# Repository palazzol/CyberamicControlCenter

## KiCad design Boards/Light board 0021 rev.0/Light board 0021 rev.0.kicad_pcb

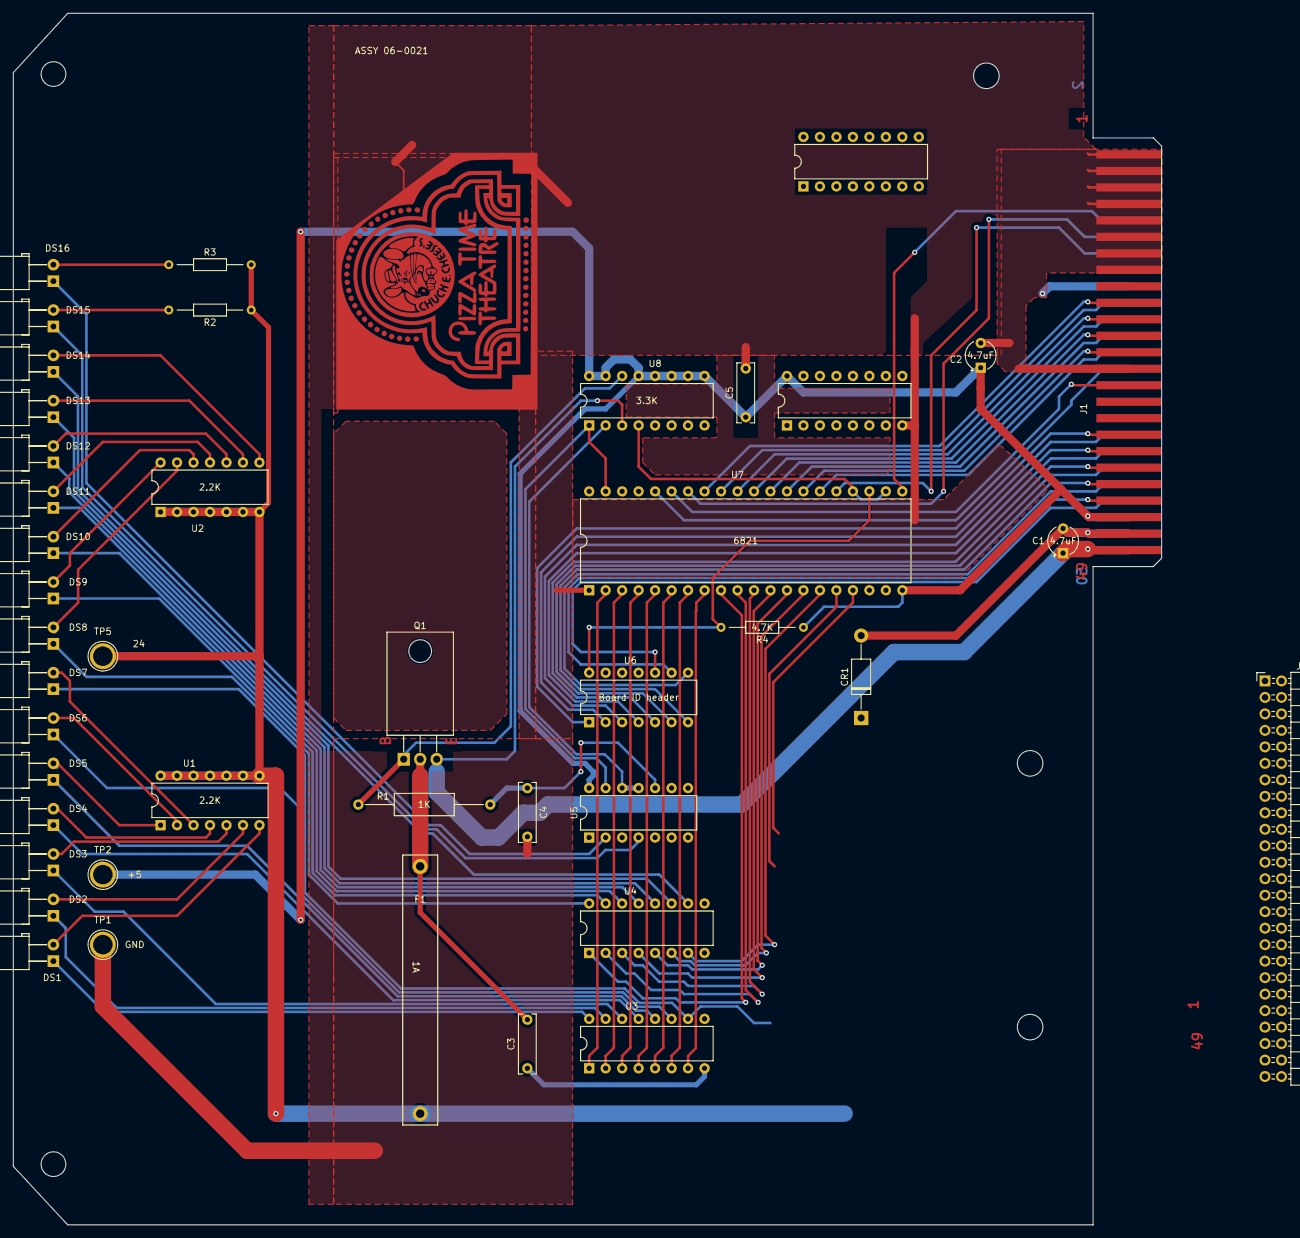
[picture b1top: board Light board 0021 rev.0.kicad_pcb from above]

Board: 2 copper layers, 176.9 x 186.7 mm, 43 parts (0 on the bottom side), 83 nets.

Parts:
C1, C2: 4.7uF; CP_Radial_Tantal_D4mm_P3.81mm
C3, C4, C5: 10nF; C_Rect_L9.0mm_W2.5mm_P7.50mm_MKT
CR1: 1N4001; D_DO-41_SOD81_P12.70mm_Horizontal
DS1, DS2, DS3, DS4, DS5, DS6, DS7, DS8, DS9, DS10, DS11, DS12, DS13, DS14, DS15, DS16: LED; LED_D5.0mm_Horizontal_O3.81mm_Z15.0mm reversed
F1: 1A; Fuseholder_Littelfuse_445_030_series_5x30mm
J1: card edge; Chuck_E_Cheese_small_card_edge
J2: light connector; PinHeader_2x25_P2.54mm_Horizontal
Q1: 2N6125; TO-220-3_Horizontal_TabDown
R1: 1K; R_Axial_DIN0309_L9.0mm_D3.2mm_P20.32mm_Horizontal
R2, R3: 2.2K; R_Axial_DIN0204_L3.6mm_D1.6mm_P12.7mm_Horizontal
R4: 4.7K; R_Axial_DIN0204_L3.6mm_D1.6mm_P12.7mm_Horizontal
TP1: GND; TestPoint_Plated_Hole_D3.0mm
TP2: +5; TestPoint_Plated_Hole_D3.0mm
TP5: 24; TestPoint_Plated_Hole_D3.0mm
U1, U2: 2.2K; DIP-14_W7.62mm
U3, U4: ULN2003A; DIP-16_W7.62mm
U5: 7406; DIP-14_W7.62mm
U6: Board ID header; DIP-14_W7.62mm
U7: 6821; DIP-40_W15.24mm
U8: 3.3K; DIP-16_W7.62mm
U14, U16: Unused DIP; DIP-16_W7.62mm

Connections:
5V: C2.1, C5.1, J1.45, J1.46, R4.1, TP2.1, U5.14 (VCC), U7.20 (VCC), U8.9 (R8.2), U8.10 (R7.2), U8.11 (R6.2), U8.12 (R5.2), U8.13 (R4.2), U8.15 (R2.2), U8.16 (R1.2), U14.16 (R1.2)
5Vpu: U5.11, U5.12, U8.2 (R2.1)
24R: C1.2, C3.1, CR1.2 (A), J1.47, J1.48, J2.2, J2.4, J2.6, J2.8, U3.8 (GND), U4.8 (GND)
24V: C1.1, J1.49, J1.50, Q1.3 (E), U8.3 (R3.1)
24Vout: F1.2, J2.1, J2.49, R2.2, R3.2, TP5.1, U1.8 (R7.2), U1.9 (R6.2), U1.10 (R5.2), U1.11 (R4.2), U1.12 (R3.2), U1.13 (R2.2), U1.14 (R1.2), U2.1 (R1.1), U2.2 (R2.1), U2.3 (R3.1), U2.4 (R4.1), U2.5 (R5.1), U2.6 (R6.1), U2.7 (R7.1), U3.9 (COM), U4.9 (COM)
24Vpu: Q1.1 (B), R1.1, U8.14 (R3.2)
A0out: DS1.1 (K), J2.47, U3.16 (O1)
A1out: DS2.1 (K), J2.45, U3.15 (O2)
A2out: DS3.1 (K), J2.43, U3.14 (O3)
A3out: DS4.1 (K), J2.41, U3.13 (O4)
A4out: DS5.1 (K), J2.39, U3.12 (O5)
A5out: DS6.1 (K), J2.37, U3.11 (O6)
A6out: DS7.1 (K), J2.35, U3.10 (O7)
A7out: DS8.1 (K), J2.33, U4.16 (O1)
B0out: DS9.1 (K), J2.31, U4.15 (O2)
B1out: DS10.1 (K), J2.29, U4.14 (O3)
B2out: DS11.1 (K), J2.27, U4.13 (O4)
B3out: DS12.1 (K), J2.25, U4.12 (O5)
B4out: DS13.1 (K), J2.23, U4.11 (O6)
B5out: DS14.1 (K), J2.21, U4.10 (O7)
B6out: DS15.1 (K), J2.19, U5.4
B7out: DS16.1 (K), J2.17, U5.2
BA0: J1.28, U7.36 (RS0)
BA1: J1.29, U7.35 (RS1)
BS1: J1.35, U6.1
BS2: J1.36, U6.2
BS3: J1.37, U6.3
BS4: J1.38, U6.4
BS5: J1.39, U6.5
BS6: J1.40, U6.6
BS7: J1.41, U6.7
BS8: J1.42, U6.8
BS9: J1.43, U6.9
BS10: J1.44, U6.10
CA2: U5.13, U7.39 (CA2), U8.1 (R1.1)
CS: U7.22 (CS0), U7.24 (CS1), U8.4 (R4.1)
DBB0: J1.19, U7.33 (D0)
DBB1: J1.20, U7.32 (D1)
DBB2: J1.21, U7.31 (D2)
DBB3: J1.22, U7.30 (D3)
DBB4: J1.23, U7.29 (D4)
DBB5: J1.24, U7.28 (D5)
DBB6: J1.25, U7.27 (D6)
DBB7: J1.26, U7.26 (D7)
GND: C2.2, C4.2, C5.2, CR1.1 (K), J1.1, J1.3, J1.5, J1.7, J1.9, J1.11, J1.13, J1.15, J1.18, J1.27, TP1.1, U5.7 (GND), U7.1 (VSS), U14.8 (R8.1)
unnamed: C4.1, R1.2, U5.10
unnamed: DS1.2 (A), U1.7 (R7.1)
unnamed: DS2.2 (A), U1.6 (R6.1)
unnamed: DS3.2 (A), U1.5 (R5.1)
unnamed: DS4.2 (A), U1.4 (R4.1)
unnamed: DS5.2 (A), U1.1 (R1.1)
unnamed: DS6.2 (A), U1.2 (R2.1)
unnamed: DS7.2 (A), U1.3 (R3.1)
unnamed: DS8.2 (A), U2.13 (R2.2)
unnamed: DS9.2 (A), U2.14 (R1.2)
unnamed: DS10.2 (A), U2.12 (R3.2)
unnamed: DS11.2 (A), U2.11 (R4.2)
unnamed: DS12.2 (A), U2.10 (R5.2)
unnamed: DS13.2 (A), U2.9 (R6.2)
unnamed: DS14.2 (A), U2.8 (R7.2)
unnamed: DS15.2 (A), R2.1
unnamed: DS16.2 (A), R3.1
unnamed: C3.2, F1.1, Q1.2 (C)
unnamed: R4.2, U6.14, U7.23 (~CS2)
PA0: U3.1 (I1), U7.2 (PA0)
PA1: U3.2 (I2), U7.3 (PA1)
PA2: U3.3 (I3), U7.4 (PA2)
PA3: U3.4 (I4), U7.5 (PA3)
PA4: U3.5 (I5), U7.6 (PA4)
PA5: U3.6 (I6), U7.7 (PA5)
PA6: U3.7 (I7), U7.8 (PA6)
PA7: U4.1 (I1), U7.9 (PA7)
PB0: U4.2 (I2), U7.10 (PB0)
PB1: U4.3 (I3), U7.11 (PB1)
PB2: U4.4 (I4), U7.12 (PB2)
PB3: U4.5 (I5), U7.13 (PB3)
PB4: U4.6 (I6), U7.14 (PB4)
PB5: U4.7 (I7), U7.15 (PB5)
PB6: U5.3, U7.16 (PB6)
PB7: U5.1, U7.17 (PB7)
PHI2: J1.14, U7.25 (ENABLE)
R/~W: J1.10, U7.21 (R/~W)
~MRST: J1.12, U7.34 (~RESET)

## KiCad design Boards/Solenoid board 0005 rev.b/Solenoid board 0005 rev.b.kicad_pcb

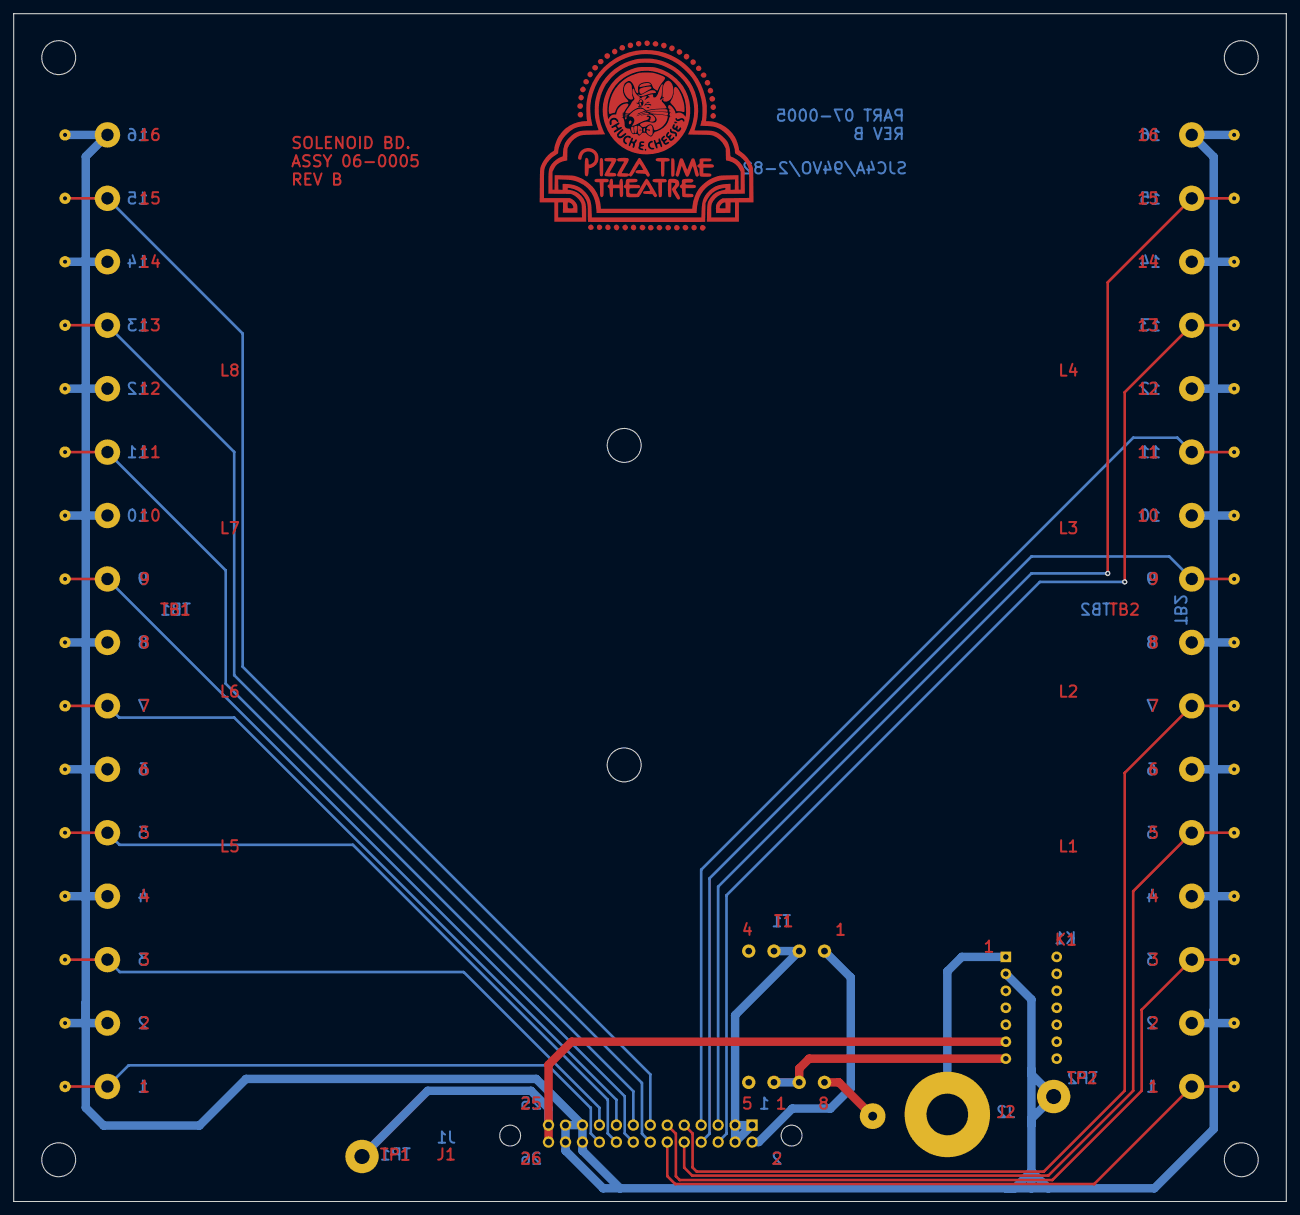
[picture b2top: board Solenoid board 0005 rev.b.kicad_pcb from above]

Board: 2 copper layers, 190.6 x 177.9 mm, 8 parts (0 on the bottom side), 23 nets.

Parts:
J1: character connector; PinHeader_2x13_P2.54mm_Horizontal
J2: Conn_Coaxial; Jack_6.35mm_Neutrik_NJ2FD-V_Vertical
K1: DIP relay; DIP-14_W7.62mm
T1: Transformer_SP_2S; Transformer_Coilcraft_Q4434-B_Rhombus-T1311
TB1, TB2: Conn_01x16_Pin; TerminalBlock_Dinkle_DT-55-B01X-16_P10.00mm
TP1: GND; TestPoint_Plated_Hole_D3.0mm
TP2: 24v; TestPoint_Plated_Hole_D3.0mm

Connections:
24R: J1.25, J1.26, K1.6, TP1.1
+24VDC: J1.21, J1.22, J1.23, J1.24, K1.2, TB1.2, TB1.4, TB1.6, TB1.8, TB1.10, TB1.12, TB1.14, TB1.16, TB2.2, TB2.4, TB2.6, TB2.8, TB2.10, TB2.12, TB2.14, TB2.16, TP2.1
AUDIO: J1.2, T1.1
CC1: J1.20, TB1.1
CC2: J1.19, TB1.3
CC3: J1.18, TB1.5
CC4: J1.17, TB1.7
CC5: J1.16, TB1.9
CC6: J1.15, TB1.11
CC7: J1.14, TB1.13
CC8: J1.13, TB1.15
LC1: J1.12, TB2.1
LC2: J1.11, TB2.3
unnamed: J2.2 (Ext), K1.1
unnamed: J2.1 (In), T1.8
unnamed: K1.7, T1.6, T1.7
SC1: J1.10, TB2.5
SC2: J1.9, TB2.7
SC3: J1.8, TB2.9
SC4: J1.7, TB2.11
SC5: J1.6, TB2.13
SC6: J1.5, TB2.15
SIGNAL GND.: J1.1, J1.3, J1.4, T1.2, T1.3

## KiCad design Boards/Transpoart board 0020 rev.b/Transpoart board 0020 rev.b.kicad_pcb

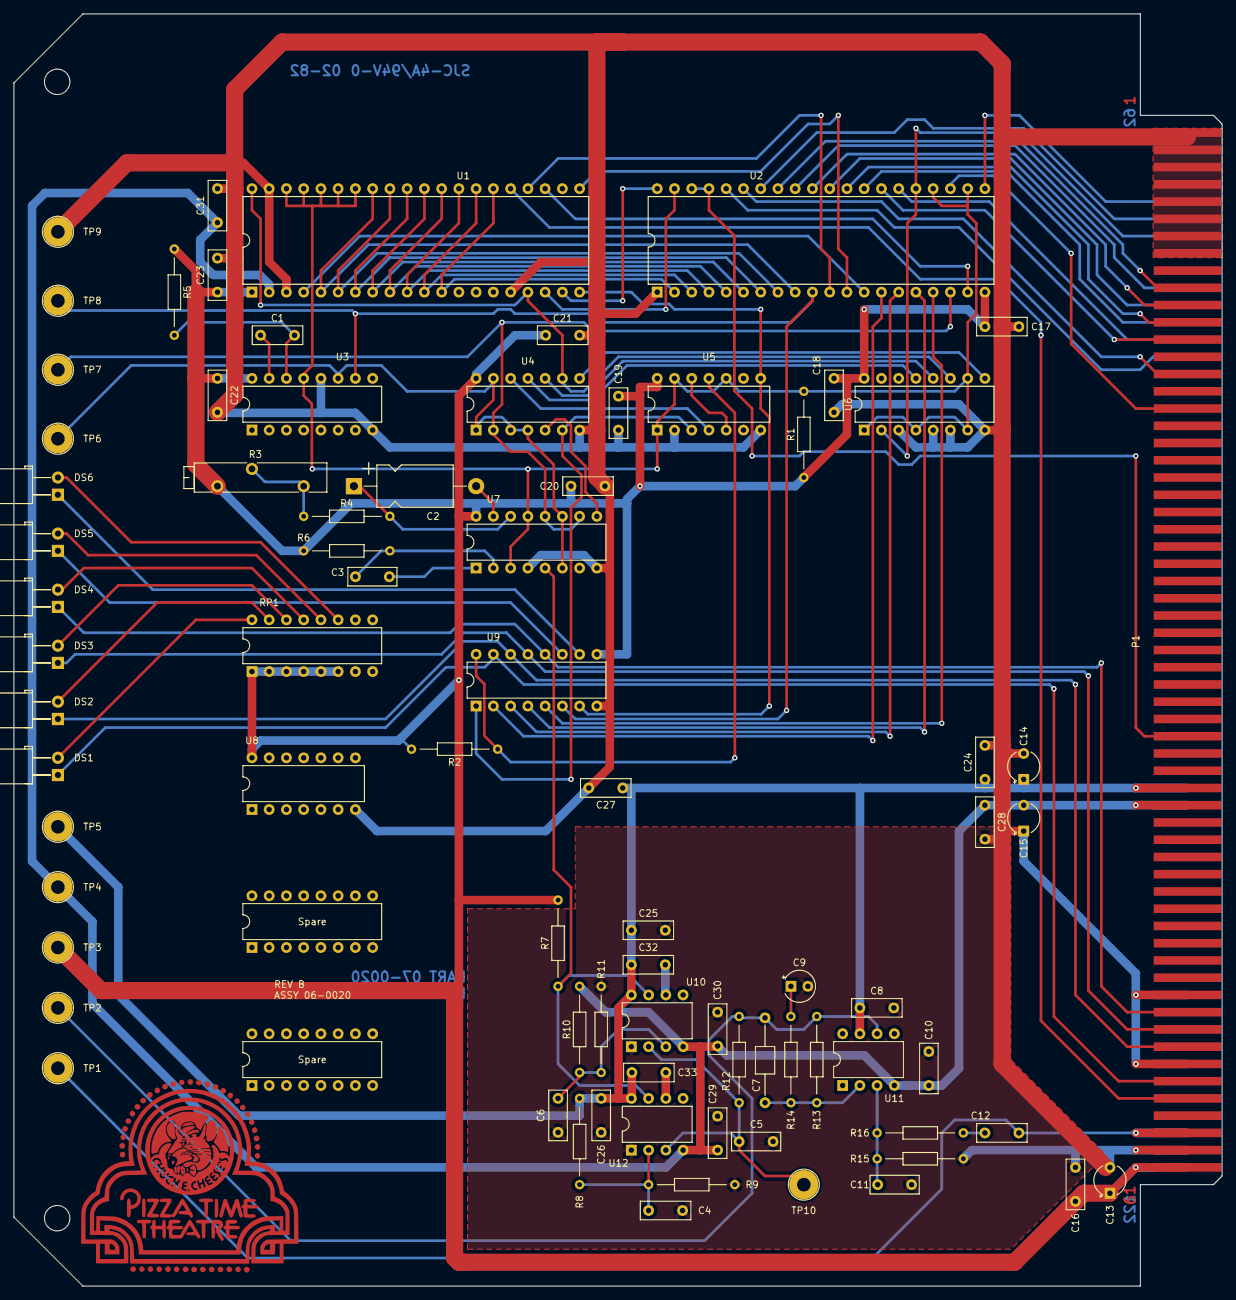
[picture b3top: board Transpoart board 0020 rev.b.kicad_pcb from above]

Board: 2 copper layers, 177.9 x 187.4 mm, 81 parts (0 on the bottom side), 83 nets.

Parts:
C1: 50nF; C_Rect_L7.2mm_W2.5mm_P5.00mm_FKS2_FKP2_MKS2_MKP2
C2: 39nF; CP_Axial_L11.0mm_D6.0mm_P18.00mm_Horizontal
C3, C5, C11: 100pF; C_Rect_L7.0mm_W2.5mm_P5.00mm
C4, C6, C8, C10, C12, C32, C33: 100nF; C_Rect_L7.2mm_W2.5mm_P5.00mm_FKS2_FKP2_MKS2_MKP2
C7: 3300pF; C_Axial_L3.8mm_D2.6mm_P12.50mm_Horizontal
C9: 4.7uF; CP_Radial_Tantal_D4.5mm_P2.50mm
C13, C14, C15: 4.7uF; CP_Radial_Tantal_D4mm_P3.81mm
C16, C17, C18, C19, C20, C21, C22, C23, C24, C25, C26, C27, C28, C29, C30, C31: 10nF; C_Rect_L7.2mm_W2.5mm_P5.00mm_FKS2_FKP2_MKS2_MKP2
DS1, DS2, DS3, DS4, DS5, DS6: LED; LED_D5.0mm_Horizontal_O3.81mm_Z15.0mm reversed
P1: CEC card edge connector large; Chuck_E_Cheese_large_card_edge
R1, R2, R14: 1K; R_Axial_DIN0204_L3.6mm_D1.6mm_P12.7mm_Horizontal
R3: 5K; Potentiometer_Bourns_3005_Horizontal
R4, R6, R12, R13, R16: 10K; R_Axial_DIN0204_L3.6mm_D1.6mm_P12.7mm_Horizontal
R5: 39K; R_Axial_DIN0204_L3.6mm_D1.6mm_P12.7mm_Horizontal
R7: 470; R_Axial_DIN0204_L3.6mm_D1.6mm_P12.7mm_Horizontal
R8, R10: 470K; R_Axial_DIN0204_L3.6mm_D1.6mm_P12.7mm_Horizontal
R9, R11: 4.7K; R_Axial_DIN0204_L3.6mm_D1.6mm_P12.7mm_Horizontal
R15: 100K; R_Axial_DIN0204_L3.6mm_D1.6mm_P12.7mm_Horizontal
RP1: 330; DIP-16_W7.62mm
TP1: AUDIO IN; TestPoint_Plated_Hole_D3.0mm
TP2: filtered audio; TestPoint_Plated_Hole_D3.0mm
TP3: +5; TestPoint_Plated_Hole_D3.0mm
TP4: -12; TestPoint_Plated_Hole_D3.0mm
TP5: +12; TestPoint_Plated_Hole_D3.0mm
TP6: zero crossings; TestPoint_Plated_Hole_D3.0mm
TP7: bits; TestPoint_Plated_Hole_D3.0mm
TP8: carrier detect; TestPoint_Plated_Hole_D3.0mm
TP9: GND; TestPoint_Plated_Hole_D3.0mm
TP10: second filtered audio; TestPoint_Plated_Hole_D3.0mm
U1: TR1602; DIP-40_W15.24mm
U2: 6821; DIP-40_W15.24mm
U3, U7: DM8602N; DIP-16_W7.62mm
U4: 7410; DIP-14_W7.62mm
U5: 74LS74; DIP-14_W7.62mm
U6: 74161; DIP-16_W7.62mm
U8: Unused DIP; DIP-14_W7.62mm
U9: ULN2003A; DIP-16_W7.62mm
U10, U12: LM311; DIP-8_W7.62mm
U11: LM741; DIP-8_W7.62mm
U14, U15: Spare; DIP-16_W7.62mm

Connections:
+5V: C13.1, C16.1, C17.1, C18.1, C19.1, C20.1, C21.1, C22.1, C23.1, P1.61, P1.122, R1.1, R2.2, R3.3, R5.1, R6.1, R7.1, RP1.1 (R1.1), RP1.2 (R2.1), RP1.3 (R3.1), RP1.4 (R4.1), RP1.5 (R5.1), RP1.6 (R6.1), TP3.1, U1.1 (VSS), U2.20 (VCC), U3.16 (VCC), U4.14 (VCC), U5.14 (VCC), U6.16 (VCC), U7.16 (VCC), U8.14 (R1.2), U9.9 (COM)
+12V: C8.1, C14.1, C24.1, C25.1, C26.1, C27.1, C32.2, C33.2, P1.39, P1.100, R8.2, TP5.1, U10.8 (V+), U11.7 (V+), U12.8 (V+)
-12V: C10.1, C15.2, C28.1, C29.1, C30.1, C31.1, P1.40, P1.101, R10.1, TP4.1, U1.2 (VGG), U10.4 (V-), U11.4 (V-), U12.4 (V-)
A0: P1.75, U2.36 (RS0)
A1: P1.15, U2.35 (RS1)
AUDIO IN: C12.1, P1.59, P1.120, TP1.1
BCLK: U1.17 (RCK), U1.40 (TCK), U4.9, U6.11 (Q3)
CA1: U1.19 (~DR), U2.40 (CA1)
CA2: U1.18 (~DDR), U2.39 (CA2)
CB1: TP7.1, U2.18 (CB1), U4.2, U7.10 (Q), U7.12 (B)
CB2: U1.23 (~THRL), U2.19 (CB2)
D0: P1.10, U2.33 (D0)
D1: P1.71, U2.32 (D1)
D2: P1.11, U2.31 (D2)
D3: P1.72, U2.30 (D3)
D4: P1.12, U2.29 (D4)
D5: P1.73, U2.28 (D5)
D6: P1.13, U2.27 (D6)
D7: P1.74, U2.26 (D7)
DATA OUT: P1.57, U1.25 (TO)
F.F.: DS2.1 (K), P1.54, U9.14 (O3)
GND: C4.2, C5.1, C6.2, C8.2, C9.2, C10.2, C11.1, C13.2, C14.2, C15.1, C16.2, C17.2, C18.2, C19.2, C20.2, C21.2, C22.2, C23.2, C24.2, C25.2, C26.2, C27.2, C28.2, C29.2, C30.2, C31.2, P1.1, P1.2, P1.3, P1.4, P1.5, P1.6, P1.7, P1.8, P1.51, P1.55, P1.60, P1.121, R9.2, R11.2, R15.2, TP9.1, U1.3 (VDD), U1.16 (SFD), U1.39 (SFE), U2.1 (VSS), U3.8 (GND), U3.12 (B), U4.7 (GND), U5.2 (D), U5.7 (GND), U6.3 (D0), U6.5 (D2), U6.6 (D3), U6.8 (GND), U7.4 (B), U7.8 (GND), U8.7 (R7.1), U9.8 (GND), U10.1 (GND), U12.1 (GND)
unnamed: C7.2, R12.1, R13.1, TP2.1, U11.6
unnamed: C9.1, R14.2
unnamed: C12.2, R16.1
unnamed: DS1.2 (A), RP1.16 (R1.2)
unnamed: DS2.2 (A), RP1.15 (R2.2)
unnamed: DS3.2 (A), RP1.14 (R3.2)
unnamed: DS4.2 (A), RP1.13 (R4.2)
unnamed: DS5.2 (A), RP1.12 (R5.2)
unnamed: DS5.1 (K), U9.11 (O6)
unnamed: DS6.2 (A), RP1.11 (R6.2)
unnamed: DS6.1 (K), U9.10 (O7)
unnamed: R3.1, R3.2, R4.1
unnamed: U1.20 (RI), U5.8 (~Q), U9.7 (I7)
unnamed: TP6.1, U3.11 (A), U4.1, U4.3, U4.4, U4.13, U7.6 (Q), U7.11 (A)
unnamed: C1.2, U3.15 (Cext)
unnamed: C1.1, R5.2, U3.14 (RCext)
unnamed: U5.5 (Q), U5.12 (D)
unnamed: U4.12, U5.4 (~S)
unnamed: U4.11, U6.13 (Q1)
unnamed: U4.10, U6.12 (Q2)
unnamed: U4.8, U6.9 (~PE)
unnamed: C2.2, U7.15 (Cext)
unnamed: C2.1, R4.2, U7.14 (RCext)
unnamed: U4.5, U7.9 (~Q)
unnamed: R7.2, U7.5 (A), U10.7, U12.7
unnamed: C3.1, U7.1 (Cext)
unnamed: C3.2, R6.2, U7.2 (RCext)
unnamed: C5.2, R12.2, TP10.1, U10.2 (+), U12.3 (-)
unnamed: C6.1, R10.2, R11.1, U10.3 (-)
unnamed: C32.1, U10.6 (STRB)
unnamed: C11.2, R15.1, R16.2, U11.3 (+)
unnamed: C7.1, R13.2, R14.1, U11.2 (-)
unnamed: C4.1, R8.1, R9.1, U12.2 (+)
unnamed: C33.1, U12.6 (STRB)
PA0: U1.12 (R0), U1.26 (T0), U2.2 (PA0)
PA1: U1.11 (R1), U1.27 (T1), U2.3 (PA1)
PA2: U1.10 (R2), U1.28 (T2), U2.4 (PA2)
PA3: U1.9 (R3), U1.29 (T3), U2.5 (PA3)
PA4: U1.8 (R4), U1.30 (T4), U2.6 (PA4)
PA5: U1.7 (R5), U1.31 (T5), U2.7 (PA5)
PA6: U1.6 (R6), U1.32 (T6), U2.8 (PA6)
PA7: U1.5 (R7), U1.33 (T7), U2.9 (PA7)
PB0: TP8.1, U2.10 (PB0), U3.10 (Q), U9.6 (I6)
PB1: U1.24 (TRE), U2.11 (PB1)
PB2: U1.21 (MR), U2.12 (PB2)
PB3: U1.4 (~RCVEN), U2.13 (PB3)
PB4: U2.14 (PB4), U9.2 (I2)
PB5: U2.15 (PB5), U9.3 (I3)
PB6: U2.16 (PB6), U9.4 (I4)
PB7: U2.17 (PB7), U9.5 (I5)
PHI2: P1.68, U2.25 (ENABLE), U6.2 (CP)
PLAY: DS4.1 (K), P1.52, U9.12 (O5)
R.W.: DS3.1 (K), P1.53, U9.13 (O4)
R/~W: P1.66, U2.21 (R/~W)
STOP: DS1.1 (K), P1.56, U9.15 (O2)
U9in: U4.6, U5.3 (C), U9.1 (I1)
U9out: R2.1, U5.11 (C), U9.16 (O1)
pup: R1.2, U1.34 (CRL), U1.35 (PI), U1.36 (SBS), U1.37 (WS1), U1.38 (WS2), U2.22 (CS0), U2.24 (CS1), U3.13 (Clr), U5.1 (~R), U5.10 (~S), U5.13 (~R), U6.1 (~MR), U6.4 (D1), U6.7 (CEP), U6.10 (CET), U7.3 (Clr), U7.13 (Clr)
/IRLQ: P1.36, U2.37 (~IRQB), U2.38 (~IRQA)
/RESET: P1.67, U2.34 (~RESET)
/SEL0: P1.17, U2.23 (~CS2)
